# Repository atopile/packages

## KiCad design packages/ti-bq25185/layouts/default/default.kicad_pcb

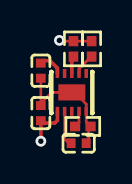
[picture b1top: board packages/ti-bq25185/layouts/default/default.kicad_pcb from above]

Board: 2 copper layers, 7 parts (0 on the bottom side), 7 nets.

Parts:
C1, C2: 1µF; C0402
C3: 10µF; C0402
R1, R2: 10kΩ; R0402
R3: 18kΩ; R0402
U1: WSON-10_L2.2-W2.0-P0.40-BL-EP_TI_DLH0010A

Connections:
ILIM_VSET: R3.1, U1.7
ISET: R1.1, U1.8
hv: C1.1, U1.2
input_cap-power-hv: C2.1, U1.10
lv: C1.2, C2.2, C3.2, R1.2, R2.2, R3.2, U1.5, U1.11
nCE: R2.1, U1.4
system_cap-power-hv: C3.1, U1.1

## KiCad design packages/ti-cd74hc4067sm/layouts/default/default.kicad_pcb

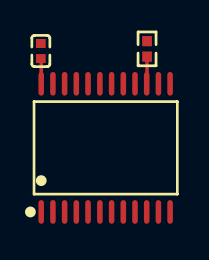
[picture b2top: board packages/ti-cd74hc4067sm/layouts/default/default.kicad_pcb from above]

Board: 2 copper layers, 3 parts (0 on the bottom side), 3 nets.

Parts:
C1: 0F; C0402
R1: 10000Ω; R0402
U1: SSOP-24_L8.1-W5.3-P0.65-LS7.8-BL

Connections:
hv: C1.1, U1.24
lv: C1.2, R1.1, U1.12
nE: R1.2, U1.15

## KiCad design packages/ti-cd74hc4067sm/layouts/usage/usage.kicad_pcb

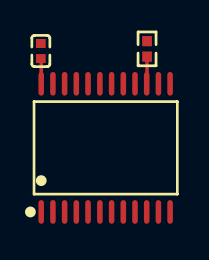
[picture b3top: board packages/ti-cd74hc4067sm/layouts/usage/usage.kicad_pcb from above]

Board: 2 copper layers, 3 parts (0 on the bottom side), 3 nets.

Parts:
C1: 0F; C0402
R1: 10000Ω; R0402
U1: SSOP-24_L8.1-W5.3-P0.65-LS7.8-BL

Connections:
hv: C1.1, U1.8, U1.24
lv: C1.2, R1.1, U1.9, U1.12
nE: R1.2, U1.15

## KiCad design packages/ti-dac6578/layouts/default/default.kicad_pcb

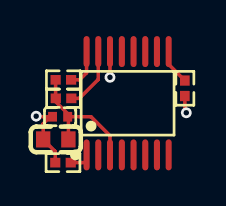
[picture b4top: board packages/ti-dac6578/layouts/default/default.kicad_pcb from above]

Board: 2 copper layers, 7 parts (0 on the bottom side), 6 nets.

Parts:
C1: 10µF; C0603
C2: 100nF; C0402
R1, R2: 4.7kΩ; R0402
R3, R4: 10kΩ; R0402
U1: TSSOP-16_L5.0-W4.4-P0.65-LS6.4-BL

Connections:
SCL: R1.1, U1.16
SDA: R2.1, U1.15
hv: C1.1, C2.1, R1.2, R2.2, U1.3
lv: C1.2, C2.2, R3.2, R4.2, U1.14
nCLR: R3.1, U1.9
nLDAC: R4.1, U1.1

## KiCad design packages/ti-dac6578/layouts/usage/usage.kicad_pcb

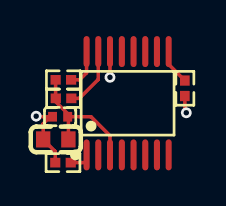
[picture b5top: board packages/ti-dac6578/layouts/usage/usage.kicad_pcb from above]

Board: 2 copper layers, 7 parts (0 on the bottom side), 6 nets.

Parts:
C1: 10µF; C0603
C2: 100nF; C0402
R1, R2: 10kΩ; R0402
R3, R4: 4.7kΩ; R0402
U1: TSSOP-16_L5.0-W4.4-P0.65-LS6.4-BL

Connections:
SCL: R3.1, U1.16
SDA: R4.1, U1.15
hv: C1.1, C2.1, R3.2, R4.2, U1.3, U1.8
lv: C1.2, C2.2, R1.2, R2.2, U1.14
nCLR: R1.1, U1.9
nLDAC: R2.1, U1.1

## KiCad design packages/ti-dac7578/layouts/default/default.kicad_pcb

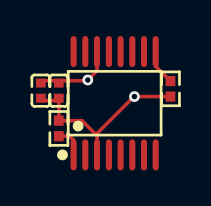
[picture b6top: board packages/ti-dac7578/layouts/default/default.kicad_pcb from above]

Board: 2 copper layers, 5 parts (0 on the bottom side), 4 nets.

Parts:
C1, C2: 1F; C0402
R1, R4: 10000Ω; R0402
U1: TSSOP-16_L5.0-W4.4-P0.65-LS6.4-BL

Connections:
hv: C1.1, C2.1, R1.1, R4.1, U1.3
lv: C1.2, C2.2, U1.2, U1.14
nCLR: R1.2, U1.9
nLDAC: R4.2, U1.1
